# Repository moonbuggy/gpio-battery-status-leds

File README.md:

# GPIO Battery Status LEDs

A little circuit board with red and green LEDs that plugs directly into a GPIO
header to indicate a status. The associated software reads a battery voltage
from an I2C/SMbus ADC and switches between the green to red LED when the voltage
crosses a specified threshold.

<!-- TOC depthFrom:2 depthTo:6 withLinks:1 updateOnSave:0 orderedList:0 -->

-   [Hardware](#hardware)
-   [Software](#software)
    -   [Installation](#installation)
    -   [Battery Monitor](#battery-monitor)
        -   [check_battery.py](#checkbatterypy)
        -   [robot-dog-battery-check.service](#robot-dog-battery-checkservice)
    -   [Robot Dog](#robot-dog)
        -   [robot-dog-server.service](#robot-dog-serverservice)
-   [Links](#links)

<!-- /TOC -->

The _battery_check.py_ script can be run standalone, but the _systemd_ service
files in this repository are aimed at a
[Freenove Robot Dog][Freenove Robot Dog Site] so they will need to be modified
if using the script in a different scenario.

The circuit board is usable as a general GPIO status indicator and it's not too
hard to modify the _systemd_ files, or create new _systemd_ files, to adapt for
an arbitrary use.

## Hardware
It's just a couple of LEDs with current limiting resistors stuck on the end of
a 2x2 pin socket.

One of the pin sockets is red, to aid alignment when attaching to the GPIO. It
fits nicely on pins 37-40 on a Raspberry Pi GPIO header, but will work anywhere
there's a pair of GPIO pins adjacent to a ground pin.

## Software
### Installation
The _install.sh_ script is specific to the Freenvove Robot dog, installing
_systemd_ unit files for both the battery monitoring service and the server
software that allows control of the robot.

Usage:
```sh
sudo ./install.sh (<path_to_freenove_software>)
```

The directory the script is executed from will be used as the path for the
Freenove software if none is provided as an argument.

The _install.sh_ script can be used as a guide for manual installation, if the
application isn't a robot dog or some components aren't desired for whatever
reason.

### Battery Monitor
#### check_battery.py
The _check_battery.py_ script simply runs a loop, reading ADC data on a delay
(5 seconds by default) and comparing it against a threshold value, then toggles
the LEDs when the threshold is crossed. As is, the script will enable the green
LED when the battery voltage is above the threshold (i.e charged) and switch to
the red LED when the battery voltage is below the threshold (i.e. low capacity).

Usage:
```sh
./check_battery.py
```

By default the script looks for an ADS7830 ADC at address _0x48_ on _SMBus 1_.

Variables, including the specific GPIO pins to use and the addressing of the
ADC, are defined at the top of the script and are easily changed. A class for a
different ADC shouldn't be hard to add.

The units (volts) are only present in the log output and don't impact data
processing, so it's just a matter of changing some log message strings to
display the right units if monitoring something other than voltage.

#### robot-dog-battery-check.service
The _robot-dog-battery-check.service_ systemd unit file will start the battery
monitor, however it is configured for the Freenove robot dog and is thus tied
to the _robot-dog-server.service_. The unit file will work standalone if the
```BindsTo=``` and ```After=``` lines are removed.

Bound to the robot dog control server as it is, the _check_battery.py_ service
won't start until the control software is started and will stop if the control
software is stopped. This provides a third LED state, with both LEDs off being
an indication that the robot dog is not ready to be controlled.

### Robot Dog
#### robot-dog-server.service
The Freenove robot dog comes with instructions to start the server inside a GUI,
after the GUI is up. If we choose to start the control software in _systemd_,
instead of during the desktop GUI's initialisation, we have the option of
disabling the GUI entirely and saving some resources and maybe improving battery
life.

The _robot-dog-server.service_ needs to be modified to add the path to the
Freenove software, although this will be done automatically if using
_install.sh_ to install everything.

## Links
### Freenove Robot Dog
*   [Freenove][Freenove Robot Dog Site]
*   [Github][Freenove Robot Dog Github]

### Datasheets
*   [ADS7830](https://www.ti.com/lit/gpn/ADS7830)

[Freenove Robot Dog Site]: https://store.freenove.com/products/fnk0050
[Freenove Robot Dog Github]: https://github.com/Freenove/Freenove_Robot_Dog_Kit_for_Raspberry_Pi

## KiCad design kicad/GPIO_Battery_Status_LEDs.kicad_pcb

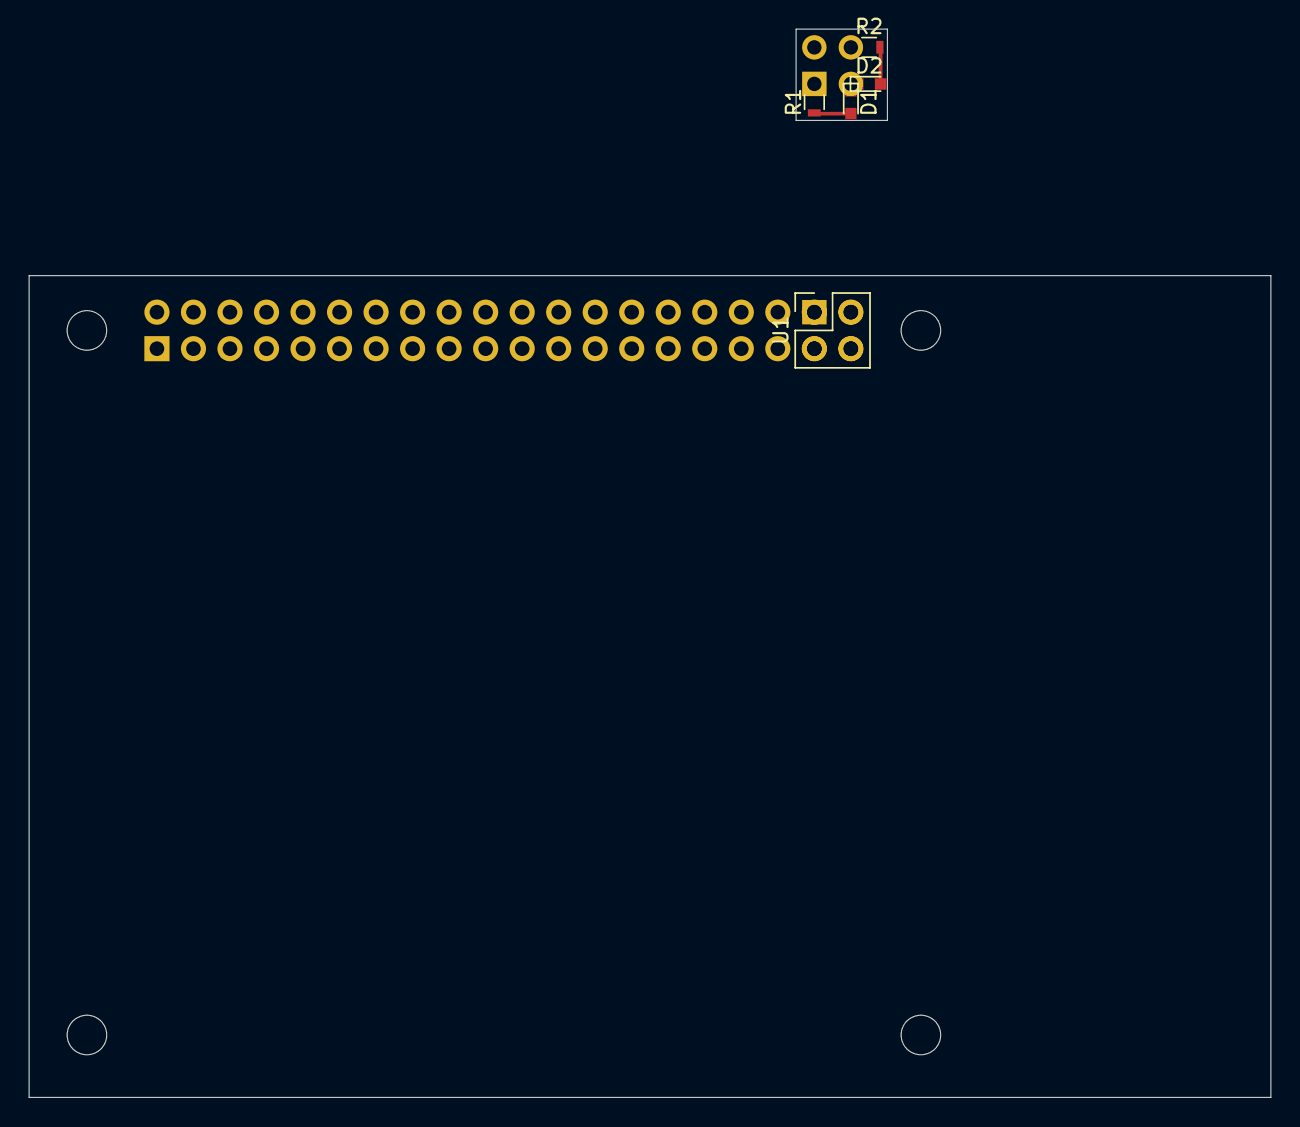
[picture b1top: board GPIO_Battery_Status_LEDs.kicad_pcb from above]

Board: 2 copper layers, 86.4 x 74.3 mm, 7 parts (1 on the bottom side), 5 nets.

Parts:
D1: LED_Red; LED_0603
D2: LED_Green; LED_0603
J1: Conn_02x02_Odd_Even; Socket_Strip_Straight_2x02_Pitch2.54mm-1-red
R1: 15k; R_0603
R2: 100k; R_0603
RPi1: Raspberry_Pi_2_3; raspberrypi_2_3
U1: GPIO_Status_LEDs

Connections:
BAT_LOW: J1.1, R1.2, RPi1.37, U1.2
BAT_OK: J1.4, R2.1, RPi1.40, U1.3
GND: D1.1, D2.1, J1.3, RPi1.39, U1.4
unnamed: D1.2, R1.1
unnamed: D2.2, R2.2
